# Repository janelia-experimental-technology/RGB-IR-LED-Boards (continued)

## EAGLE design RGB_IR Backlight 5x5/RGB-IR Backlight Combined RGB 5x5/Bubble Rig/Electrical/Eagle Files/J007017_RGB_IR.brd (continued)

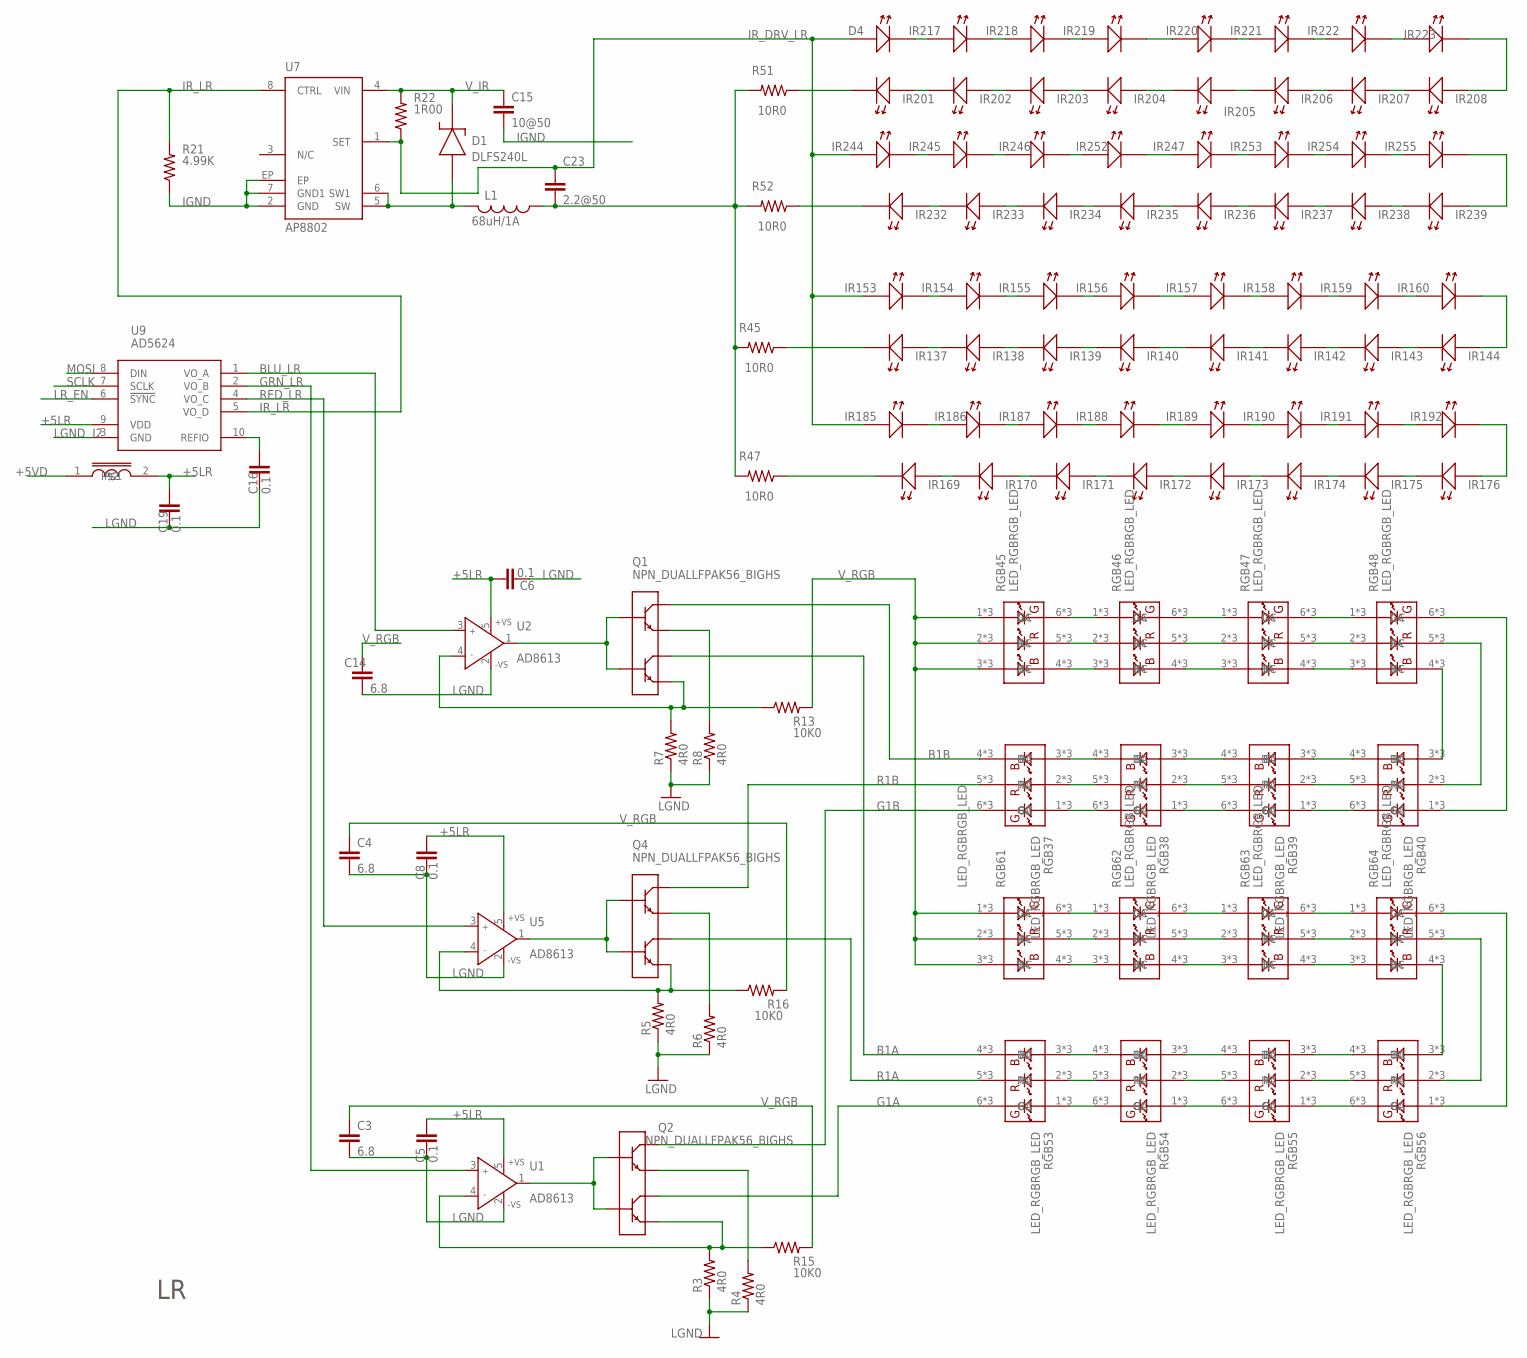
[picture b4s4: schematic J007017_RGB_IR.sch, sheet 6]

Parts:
C3, C4, C14: 6.8; 1210S
C5, C6, C8, C16, C19: 0.1; 0603S
C15: 10@50; 1210S
C23: 2.2@50; 1206S
D1: DLFS240L; PWRDI-123
D4: LEDLED_SFH4050_HEAT; LED_SFH4050_HEAT
I2: INDUCTOR0805S; 0805S
IR137, IR255: LEDLED_SFH4050; LED_SFH4050
IR138, IR139, IR140, IR141, IR142, IR143, IR144, IR153, IR155, IR156, IR157, IR158, IR159, IR160, IR169, IR170, IR171, IR172, IR173, IR174, IR175, IR176, IR185, IR186, IR187, IR188, IR189, IR190, IR191, IR192, IR201, IR202, IR203, IR204, IR205, IR206, IR207, IR208, IR217, IR218, IR219, IR220, IR221, IR222, IR223, IR232, IR233, IR234, IR235, IR236, IR237, IR238, IR239, IR244, IR245, IR246, IR247, IR252, IR253, IR254: LEDLED_SFH4050_HEAT; LED_SFH4050_HEAT
IR154: LEDLED_SFH4050_A; LED_SFH4045_HEAT_A
L1: 68uH/1A; SRU8043
Q1, Q2, Q4: NPN_DUALLFPAK56_BIGHS; LFPAK56_HS2
R3, R4, R5, R6, R7, R8: 4R0; 1812
R13, R15, R16: 10K0; 1206S
R21: 4.99K; 0805S
R22: 1R00; 1206S
R45, R47, R51, R52: 10R0; 1206S
RGB37, RGB38, RGB39, RGB40, RGB45, RGB46, RGB47, RGB48, RGB53, RGB54, RGB55, RGB56, RGB61, RGB62, RGB63, RGB64: LED_RGBRGB_LED; OVSPRGB_HS_FIXED
U1, U2, U5: AD8613; SOT23-5
U7: AP8802; SOIC8-EP
U9: AD5624; MSOP10

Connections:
+5LR: C5.1, C6.1, C8.1, C19.1, I2.2, U1.5 (+VS), U2.5 (+VS), U5.5 (+VS), U9.9 (VDD)
+5VD: I2.1; also elsewhere on the board
B1A: Q1.5 (C2), Q1.5A (C2), Q1.5A1 (C2), Q1.5B (C2), Q1.5C (C2), Q1.5C1 (C2), Q1.5C2 (C2), Q1.6 (C2), Q1.56 (C2), Q1.56A (C2), Q1.56B (C2), RGB53.4 (BC), RGB53.4A (BC), RGB53.4B (BC)
B1B: Q1.7 (C1), Q1.8 (C1), Q1.8A (C1), Q1.8B (C1), Q1.8C (C1), Q1.8C1 (C1), Q1.8C2 (C1), Q1.8C3 (C1), Q1.78 (C1), Q1.78A (C1), Q1.78B (C1), RGB37.4 (BC), RGB37.4A (BC), RGB37.4B (BC)
BLU_LR: U2.3 (IN+), U9.1 (VO_A)
G1A: Q2.5 (C2), Q2.5A (C2), Q2.5A1 (C2), Q2.5B (C2), Q2.5C (C2), Q2.5C1 (C2), Q2.5C2 (C2), Q2.6 (C2), Q2.56 (C2), Q2.56A (C2), Q2.56B (C2), RGB53.6 (GC), RGB53.6A (GC), RGB53.6B (GC)
G1B: Q2.7 (C1), Q2.8 (C1), Q2.8A (C1), Q2.8B (C1), Q2.8C (C1), Q2.8C1 (C1), Q2.8C2 (C1), Q2.8C3 (C1), Q2.78 (C1), Q2.78A (C1), Q2.78B (C1), RGB37.6 (GC), RGB37.6A (GC), RGB37.6B (GC)
GRN_LR: U1.3 (IN+), U9.2 (VO_B)
IGND: C15.2, R21.1, U7.2 (GND), U7.7 (GND1), U7.EP; also elsewhere on the board
IR_DRV_LR: C23.1, D4.A, D4.A1 (A), IR153.A, IR153.A1 (A), IR185.A, IR185.A1 (A), IR244.A, IR244.A1 (A), R22.1, U7.1 (SET)
IR_LR: R21.2, U7.8 (CTRL), U9.5 (VO_D)
IR_RET_UL3: C23.2, L1.1, R45.2, R47.2, R51.2, R52.2
LGND: C3.2, C4.2, C5.2, C6.2, C8.2, C14.2, C16.2, C19.2, R3.1, R4.1, R5.1, R6.1, R7.1, R8.1, U1.2 (-VS), U2.2 (-VS), U5.2 (-VS), U9.3 (GND); also elsewhere on the board
LR_EN: U9.6 (!SYNC); also elsewhere on the board
MOSI: U9.8 (DIN); also elsewhere on the board
unnamed: C16.1, U9.10 (REFIO)
unnamed: IR143.A, IR143.A1 (A), IR144.C (K), IR144.C1 (K)
unnamed: IR142.A, IR142.A1 (A), IR143.C (K), IR143.C1 (K)
unnamed: IR141.A, IR141.A1 (A), IR142.C (K), IR142.C1 (K)
unnamed: IR139.A, IR139.A1 (A), IR140.C (K), IR140.C1 (K)
unnamed: IR138.A, IR138.A1 (A), IR139.C (K), IR139.C1 (K)
unnamed: IR137.A, IR138.C (K), IR138.C1 (K)
unnamed: IR153.C (K), IR153.C1 (K), IR154.A, IR154.A1 (A)
unnamed: IR154.C (K), IR155.A, IR155.A1 (A)
unnamed: IR155.C (K), IR155.C1 (K), IR156.A, IR156.A1 (A)
unnamed: IR140.A, IR140.A1 (A), IR141.C (K), IR141.C1 (K)
unnamed: IR175.A, IR175.A1 (A), IR176.C (K), IR176.C1 (K)
unnamed: IR174.A, IR174.A1 (A), IR175.C (K), IR175.C1 (K)
unnamed: IR173.A, IR173.A1 (A), IR174.C (K), IR174.C1 (K)
unnamed: IR172.A, IR172.A1 (A), IR173.C (K), IR173.C1 (K)
unnamed: IR171.A, IR171.A1 (A), IR172.C (K), IR172.C1 (K)
unnamed: IR170.A, IR170.A1 (A), IR171.C (K), IR171.C1 (K)
unnamed: IR169.A, IR169.A1 (A), IR170.C (K), IR170.C1 (K)
unnamed: IR157.C (K), IR157.C1 (K), IR158.A, IR158.A1 (A)
unnamed: IR158.C (K), IR158.C1 (K), IR159.A, IR159.A1 (A)
unnamed: IR159.C (K), IR159.C1 (K), IR160.A, IR160.A1 (A)
unnamed: IR185.C (K), IR185.C1 (K), IR186.A, IR186.A1 (A)
unnamed: IR186.C (K), IR186.C1 (K), IR187.A, IR187.A1 (A)
unnamed: IR187.C (K), IR187.C1 (K), IR188.A, IR188.A1 (A)
unnamed: IR189.C (K), IR189.C1 (K), IR190.A, IR190.A1 (A)
unnamed: IR190.C (K), IR190.C1 (K), IR191.A, IR191.A1 (A)
unnamed: IR191.C (K), IR191.C1 (K), IR192.A, IR192.A1 (A)
unnamed: IR156.C (K), IR156.C1 (K), IR157.A, IR157.A1 (A)
unnamed: IR144.A, IR144.A1 (A), IR160.C (K), IR160.C1 (K)
unnamed: IR188.C (K), IR188.C1 (K), IR189.A, IR189.A1 (A)
unnamed: IR176.A, IR176.A1 (A), IR192.C (K), IR192.C1 (K)
unnamed: IR137.C (K), R45.1
unnamed: IR169.C (K), IR169.C1 (K), R47.1
unnamed: IR207.A, IR207.A1 (A), IR208.C (K), IR208.C1 (K)
unnamed: IR206.A, IR206.A1 (A), IR207.C (K), IR207.C1 (K)
unnamed: IR205.A, IR205.A1 (A), IR206.C (K), IR206.C1 (K)
unnamed: IR203.A, IR203.A1 (A), IR204.C (K), IR204.C1 (K)
unnamed: IR202.A, IR202.A1 (A), IR203.C (K), IR203.C1 (K)
unnamed: IR201.A, IR201.A1 (A), IR202.C (K), IR202.C1 (K)
unnamed: D4.C (K), D4.C1 (K), IR217.A, IR217.A1 (A)
unnamed: IR217.C (K), IR217.C1 (K), IR218.A, IR218.A1 (A)
unnamed: IR218.C (K), IR218.C1 (K), IR219.A, IR219.A1 (A)
unnamed: IR204.A, IR204.A1 (A), IR205.C (K), IR205.C1 (K)
unnamed: IR238.A, IR238.A1 (A), IR239.C (K), IR239.C1 (K)
unnamed: IR237.A, IR237.A1 (A), IR238.C (K), IR238.C1 (K)
unnamed: IR236.A, IR236.A1 (A), IR237.C (K), IR237.C1 (K)
unnamed: IR235.A, IR235.A1 (A), IR236.C (K), IR236.C1 (K)
unnamed: IR234.A, IR234.A1 (A), IR235.C (K), IR235.C1 (K)
unnamed: IR233.A, IR233.A1 (A), IR234.C (K), IR234.C1 (K)
unnamed: IR232.A, IR232.A1 (A), IR233.C (K), IR233.C1 (K)
unnamed: IR220.C (K), IR220.C1 (K), IR221.A, IR221.A1 (A)
unnamed: IR221.C (K), IR221.C1 (K), IR222.A, IR222.A1 (A)
unnamed: IR222.C (K), IR222.C1 (K), IR223.A, IR223.A1 (A)
unnamed: IR244.C (K), IR244.C1 (K), IR245.A, IR245.A1 (A)
unnamed: IR245.C (K), IR245.C1 (K), IR246.A, IR246.A1 (A)
unnamed: IR246.C (K), IR246.C1 (K), IR252.A, IR252.A1 (A)
unnamed: IR247.C (K), IR247.C1 (K), IR253.A, IR253.A1 (A)
unnamed: IR253.C (K), IR253.C1 (K), IR254.A, IR254.A1 (A)
unnamed: IR254.C (K), IR254.C1 (K), IR255.A
unnamed: IR219.C (K), IR219.C1 (K), IR220.A, IR220.A1 (A)
unnamed: IR208.A, IR208.A1 (A), IR223.C (K), IR223.C1 (K)
unnamed: IR247.A, IR247.A1 (A), IR252.C (K), IR252.C1 (K)
unnamed: IR239.A, IR239.A1 (A), IR255.C (K)
unnamed: IR201.C (K), IR201.C1 (K), R51.1
unnamed: IR232.C (K), IR232.C1 (K), R52.1
unnamed: Q1.3 (E2), R7.2, R13.1, U2.4 (IN-)
unnamed: D1.A, L1.2, U7.5 (SW), U7.6 (SW1)
unnamed: Q4.3 (E2), R5.2, R16.1, U5.4 (IN-)
unnamed: Q4.2 (B1), Q4.4 (B2), U5.1 (OUT)
unnamed: RGB45.6 (GC), RGB45.6A (GC), RGB45.6B (GC), RGB46.1 (GA), RGB46.1A (GA), RGB46.1B (GA)
unnamed: RGB45.5 (RC), RGB45.5A (RC), RGB45.5B (RC), RGB46.2 (RA), RGB46.2A (RA), RGB46.2B (RA)
unnamed: RGB45.4 (BC), RGB45.4A (BC), RGB45.4B (BC), RGB46.3 (BA), RGB46.3A (BA), RGB46.3B (BA)
unnamed: RGB46.6 (GC), RGB46.6A (GC), RGB46.6B (GC), RGB47.1 (GA), RGB47.1A (GA), RGB47.1B (GA)
unnamed: RGB46.5 (RC), RGB46.5A (RC), RGB46.5B (RC), RGB47.2 (RA), RGB47.2A (RA), RGB47.2B (RA)
unnamed: RGB46.4 (BC), RGB46.4A (BC), RGB46.4B (BC), RGB47.3 (BA), RGB47.3A (BA), RGB47.3B (BA)
unnamed: RGB47.6 (GC), RGB47.6A (GC), RGB47.6B (GC), RGB48.1 (GA), RGB48.1A (GA), RGB48.1B (GA)
unnamed: RGB47.5 (RC), RGB47.5A (RC), RGB47.5B (RC), RGB48.2 (RA), RGB48.2A (RA), RGB48.2B (RA)
unnamed: RGB47.4 (BC), RGB47.4A (BC), RGB47.4B (BC), RGB48.3 (BA), RGB48.3A (BA), RGB48.3B (BA)
unnamed: RGB40.1 (GA), RGB40.1A (GA), RGB40.1B (GA), RGB48.6 (GC), RGB48.6A (GC), RGB48.6B (GC)
unnamed: RGB40.2 (RA), RGB40.2A (RA), RGB40.2B (RA), RGB48.5 (RC), RGB48.5A (RC), RGB48.5B (RC)
unnamed: RGB40.3 (BA), RGB40.3A (BA), RGB40.3B (BA), RGB48.4 (BC), RGB48.4A (BC), RGB48.4B (BC)
unnamed: RGB39.1 (GA), RGB39.1A (GA), RGB39.1B (GA), RGB40.6 (GC), RGB40.6A (GC), RGB40.6B (GC)
unnamed: RGB39.2 (RA), RGB39.2A (RA), RGB39.2B (RA), RGB40.5 (RC), RGB40.5A (RC), RGB40.5B (RC)
unnamed: RGB39.3 (BA), RGB39.3A (BA), RGB39.3B (BA), RGB40.4 (BC), RGB40.4A (BC), RGB40.4B (BC)
unnamed: RGB38.1 (GA), RGB38.1A (GA), RGB38.1B (GA), RGB39.6 (GC), RGB39.6A (GC), RGB39.6B (GC)
unnamed: RGB38.2 (RA), RGB38.2A (RA), RGB38.2B (RA), RGB39.5 (RC), RGB39.5A (RC), RGB39.5B (RC)
unnamed: RGB38.3 (BA), RGB38.3A (BA), RGB38.3B (BA), RGB39.4 (BC), RGB39.4A (BC), RGB39.4B (BC)
unnamed: RGB37.1 (GA), RGB37.1A (GA), RGB37.1B (GA), RGB38.6 (GC), RGB38.6A (GC), RGB38.6B (GC)
unnamed: RGB37.2 (RA), RGB37.2A (RA), RGB37.2B (RA), RGB38.5 (RC), RGB38.5A (RC), RGB38.5B (RC)
unnamed: RGB37.3 (BA), RGB37.3A (BA), RGB37.3B (BA), RGB38.4 (BC), RGB38.4A (BC), RGB38.4B (BC)
unnamed: Q2.3 (E2), R3.2, R15.1, U1.4 (IN-)
unnamed: Q2.2 (B1), Q2.4 (B2), U1.1 (OUT)
unnamed: RGB61.6 (GC), RGB61.6A (GC), RGB61.6B (GC), RGB62.1 (GA), RGB62.1A (GA), RGB62.1B (GA)
unnamed: RGB61.5 (RC), RGB61.5A (RC), RGB61.5B (RC), RGB62.2 (RA), RGB62.2A (RA), RGB62.2B (RA)
unnamed: RGB61.4 (BC), RGB61.4A (BC), RGB61.4B (BC), RGB62.3 (BA), RGB62.3A (BA), RGB62.3B (BA)
unnamed: RGB62.6 (GC), RGB62.6A (GC), RGB62.6B (GC), RGB63.1 (GA), RGB63.1A (GA), RGB63.1B (GA)
unnamed: RGB62.5 (RC), RGB62.5A (RC), RGB62.5B (RC), RGB63.2 (RA), RGB63.2A (RA), RGB63.2B (RA)
unnamed: RGB62.4 (BC), RGB62.4A (BC), RGB62.4B (BC), RGB63.3 (BA), RGB63.3A (BA), RGB63.3B (BA)
unnamed: RGB63.6 (GC), RGB63.6A (GC), RGB63.6B (GC), RGB64.1 (GA), RGB64.1A (GA), RGB64.1B (GA)
unnamed: RGB63.5 (RC), RGB63.5A (RC), RGB63.5B (RC), RGB64.2 (RA), RGB64.2A (RA), RGB64.2B (RA)
unnamed: RGB63.4 (BC), RGB63.4A (BC), RGB63.4B (BC), RGB64.3 (BA), RGB64.3A (BA), RGB64.3B (BA)
unnamed: RGB56.1 (GA), RGB56.1A (GA), RGB56.1B (GA), RGB64.6 (GC), RGB64.6A (GC), RGB64.6B (GC)
unnamed: RGB56.2 (RA), RGB56.2A (RA), RGB56.2B (RA), RGB64.5 (RC), RGB64.5A (RC), RGB64.5B (RC)
unnamed: RGB56.3 (BA), RGB56.3A (BA), RGB56.3B (BA), RGB64.4 (BC), RGB64.4A (BC), RGB64.4B (BC)
unnamed: RGB55.1 (GA), RGB55.1A (GA), RGB55.1B (GA), RGB56.6 (GC), RGB56.6A (GC), RGB56.6B (GC)
unnamed: RGB55.2 (RA), RGB55.2A (RA), RGB55.2B (RA), RGB56.5 (RC), RGB56.5A (RC), RGB56.5B (RC)
unnamed: RGB55.3 (BA), RGB55.3A (BA), RGB55.3B (BA), RGB56.4 (BC), RGB56.4A (BC), RGB56.4B (BC)
unnamed: RGB54.1 (GA), RGB54.1A (GA), RGB54.1B (GA), RGB55.6 (GC), RGB55.6A (GC), RGB55.6B (GC)
unnamed: RGB54.2 (RA), RGB54.2A (RA), RGB54.2B (RA), RGB55.5 (RC), RGB55.5A (RC), RGB55.5B (RC)
unnamed: RGB54.3 (BA), RGB54.3A (BA), RGB54.3B (BA), RGB55.4 (BC), RGB55.4A (BC), RGB55.4B (BC)
unnamed: RGB53.1 (GA), RGB53.1A (GA), RGB53.1B (GA), RGB54.6 (GC), RGB54.6A (GC), RGB54.6B (GC)
unnamed: RGB53.2 (RA), RGB53.2A (RA), RGB53.2B (RA), RGB54.5 (RC), RGB54.5A (RC), RGB54.5B (RC)
unnamed: RGB53.3 (BA), RGB53.3A (BA), RGB53.3B (BA), RGB54.4 (BC), RGB54.4A (BC), RGB54.4B (BC)
unnamed: Q1.2 (B1), Q1.4 (B2), U2.1 (OUT)
unnamed: Q1.1 (E1), R8.2
unnamed: Q4.1 (E1), R6.2
unnamed: Q2.1 (E1), R4.2
R1A: Q4.5 (C2), Q4.5A (C2), Q4.5A1 (C2), Q4.5B (C2), Q4.5C (C2), Q4.5C1 (C2), Q4.5C2 (C2), Q4.6 (C2), Q4.56 (C2), Q4.56A (C2), Q4.56B (C2), RGB53.5 (RC), RGB53.5A (RC), RGB53.5B (RC)
R1B: Q4.7 (C1), Q4.8 (C1), Q4.8A (C1), Q4.8B (C1), Q4.8C (C1), Q4.8C1 (C1), Q4.8C2 (C1), Q4.8C3 (C1), Q4.78 (C1), Q4.78A (C1), Q4.78B (C1), RGB37.5 (RC), RGB37.5A (RC), RGB37.5B (RC)
RED_LR: U5.3 (IN+), U9.4 (VO_C)
SCLK: U9.7 (SCLK); also elsewhere on the board
V_IR: C15.1, D1.K, R22.2, U7.4 (VIN); also elsewhere on the board
V_RGB: C3.1, C4.1, C14.1, R13.2, R15.2, R16.2, RGB45.1 (GA), RGB45.1A (GA), RGB45.1B (GA), RGB45.2 (RA), RGB45.2A (RA), RGB45.2B (RA), RGB45.3 (BA), RGB45.3A (BA), RGB45.3B (BA), RGB61.1 (GA), RGB61.1A (GA), RGB61.1B (GA), RGB61.2 (RA), RGB61.2A (RA), RGB61.2B (RA), RGB61.3 (BA), RGB61.3A (BA), RGB61.3B (BA); also elsewhere on the board

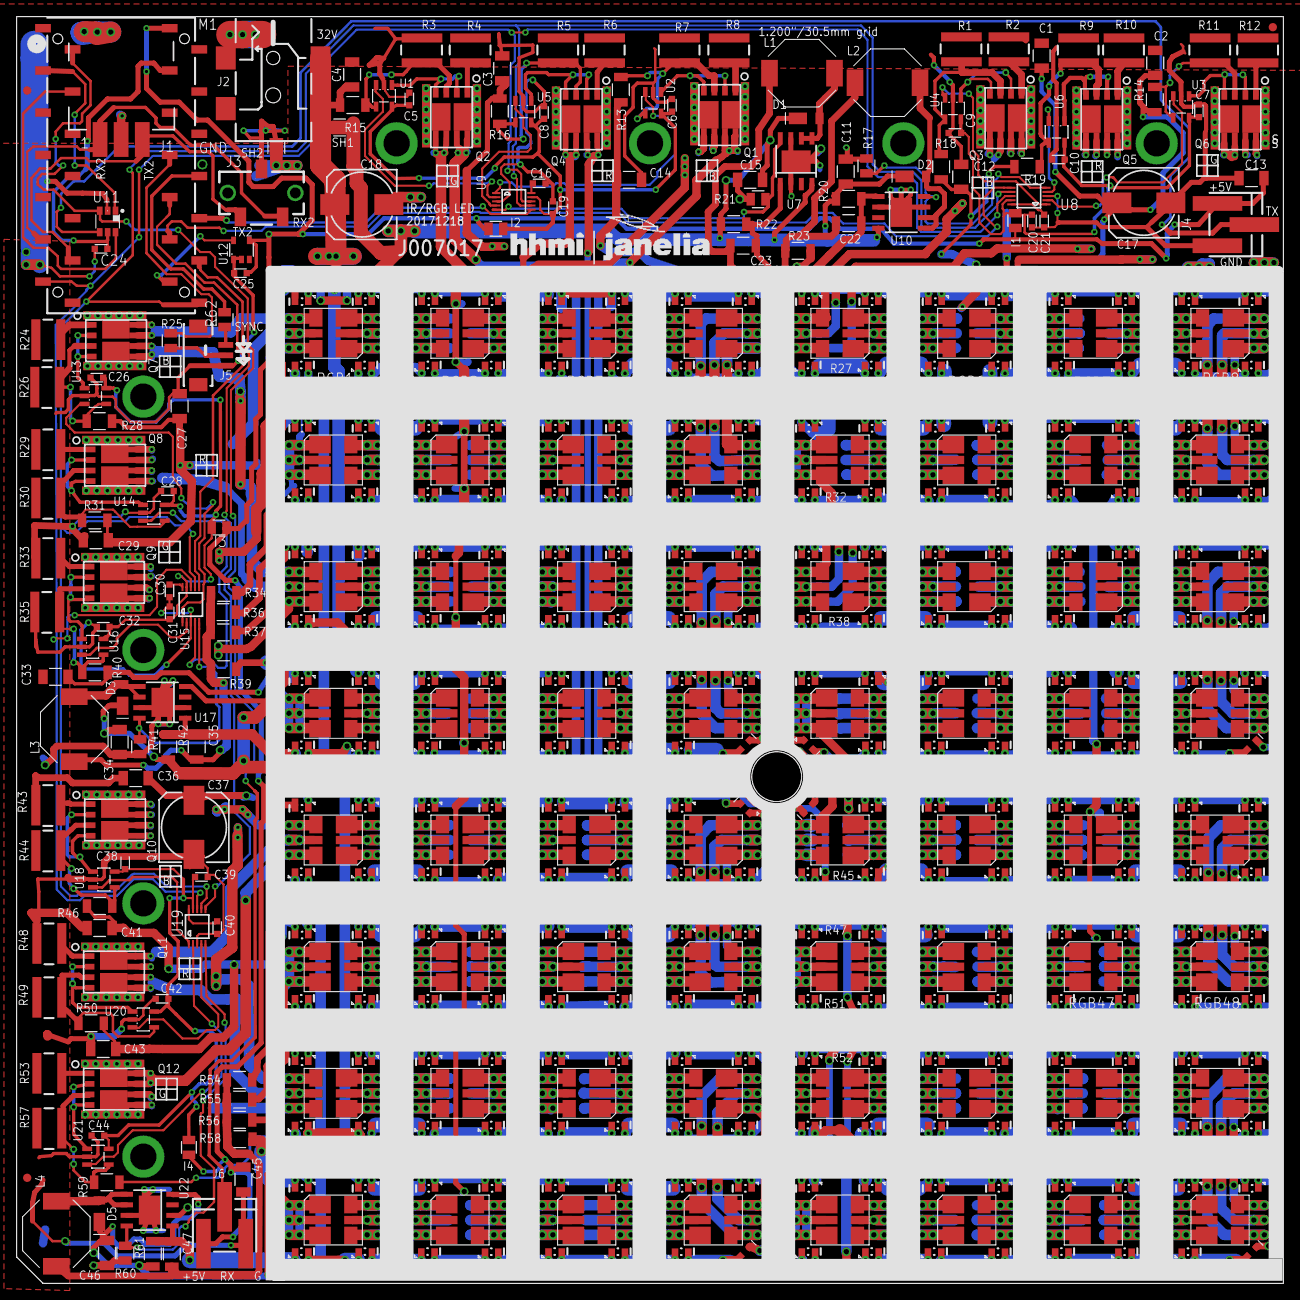
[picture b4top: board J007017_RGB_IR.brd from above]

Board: 2 copper layers, 152.4 x 152.4 mm, 488 parts (0 on the bottom side), 543 nets.

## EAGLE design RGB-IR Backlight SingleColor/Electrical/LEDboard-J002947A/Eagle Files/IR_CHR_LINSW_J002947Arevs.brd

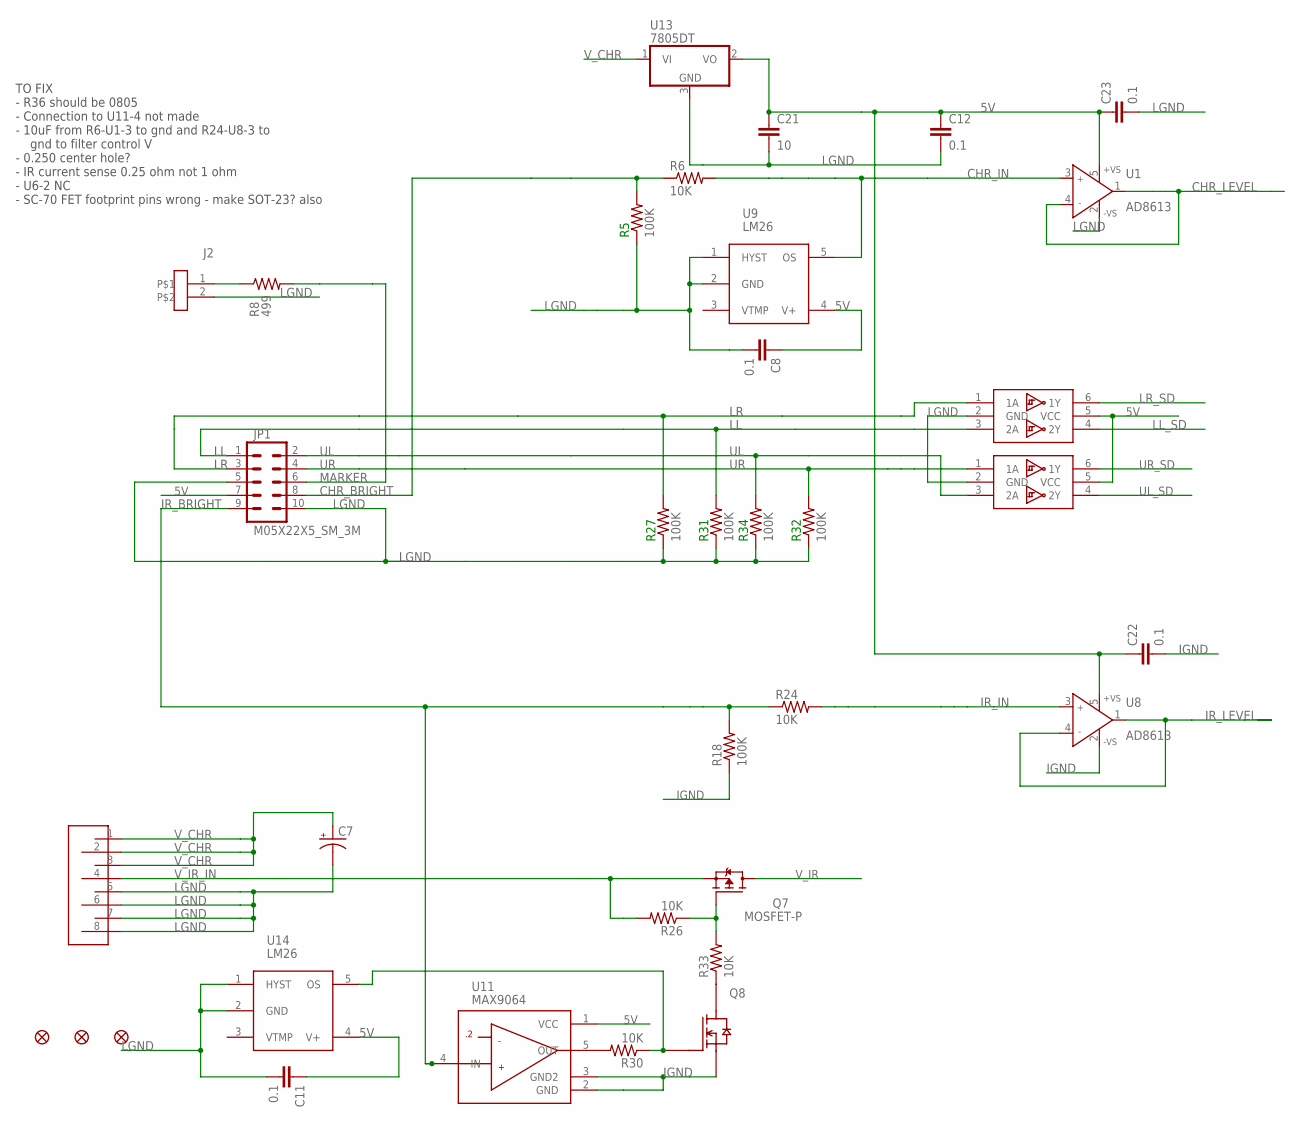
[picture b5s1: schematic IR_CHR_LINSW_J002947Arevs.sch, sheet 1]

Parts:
C7: CAP_POLG; PANASONIC_G
C8, C11, C12, C22, C23: 0.1; 0603S
C21: 10; 0805S
FID1, FID2, FID3: FIDUCIAL1.5X3; FIDUCIAL-1.5X3
J1: CON8PHOENIX1778829; PHOENIX1778829
J2: CON2DF3-2\; DF3-2_RA
JP1: M05X22X5_SM_3M; 2X5-SHROUDED_SMD_3M
Q7: MOSFET-P; SO-8POWERPAK
Q8: MOSFET-N; SC-70
R5, R18, R27, R31, R32, R34: 100K; 0603S
R6, R24, R26, R30, R33: 10K; 0603S
R8: 499; 0603S
U1, U8: AD8613; SOT23-5
U9, U14: LM26; SOT23-5
U10, U12: 74DUAL14; SOT23-6
U11: MAX9064; SOT23-5L
U13: 7805DT; TO252

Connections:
5V: C8.1, C11.1, C12.1, C21.1, C22.1, C23.1, JP1.7, U1.5 (+VS), U8.5 (+VS), U9.4 (V+), U10.5 (VCC), U11.1 (VCC), U12.5 (VCC), U13.2 (VO), U14.4 (V+)
CHR_BRIGHT: JP1.8, R5.2, R6.1
CHR_IN: R6.2, U1.3 (IN+), U9.5 (OS)
CHR_LEVEL: U1.1 (OUT), U1.4 (IN-); also elsewhere on the board
IGND: C22.2, Q8.2 (S), R18.1, U8.2 (-VS), U11.2 (GND), U11.3 (GND2); also elsewhere on the board
IR_BRIGHT: JP1.9, R18.2, R24.1, U11.4 (IN)
IR_IN: R24.2, U8.3 (IN+)
IR_LEVEL: U8.1 (OUT), U8.4 (IN-); also elsewhere on the board
LGND: C7.-, C8.2, C11.2, C12.2, C21.2, C23.2, J1.5, J1.6, J1.7, J1.8, J2.2, JP1.5, JP1.10, R5.1, R27.1, R31.1, R32.1, R34.1, U1.2 (-VS), U9.1 (HYST), U9.2 (GND), U10.2 (GND), U12.2 (GND), U13.3 (GND), U14.1 (HYST), U14.2 (GND); also elsewhere on the board
LL: JP1.1, R31.2, U10.3 (2A)
LL_SD: U10.4 (2Y); also elsewhere on the board
LR: JP1.3, R27.2, U10.1 (1A)
LR_SD: U10.6 (1Y); also elsewhere on the board
MARKER: JP1.6, R8.2
unnamed: J2.1, R8.1
unnamed: Q7.4 (G), R26.1, R33.2
unnamed: Q8.1 (G), R30.1, U14.5 (OS)
unnamed: Q8.3 (D), R33.1
unnamed: R30.2, U11.5 (OUT)
UL: JP1.2, R34.2, U12.3 (2A)
UL_SD: U12.4 (2Y); also elsewhere on the board
UR: JP1.4, R32.2, U12.1 (1A)
UR_SD: U12.6 (1Y); also elsewhere on the board
V_CHR: C7.+, J1.1, J1.2, J1.3, U13.1 (VI); also elsewhere on the board
V_IR: Q7.5 (D), Q7.6 (D), Q7.7 (D), Q7.8 (D), Q7.9 (D); also elsewhere on the board
V_IR_IN: J1.4, Q7.1 (S), Q7.2 (S), Q7.3 (S), R26.2

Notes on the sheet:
TO FIX - R36 should be 0805 - Connection to U11-4 not made - 10uF from R6-U1-3 to gnd and R24-U8-3 to gnd to filter control V - 0.250 center hole? - IR current sense 0.25 ohm not 1 ohm - U6-2 NC - SC-70 FET footprint pins wrong - make SOT-23? also

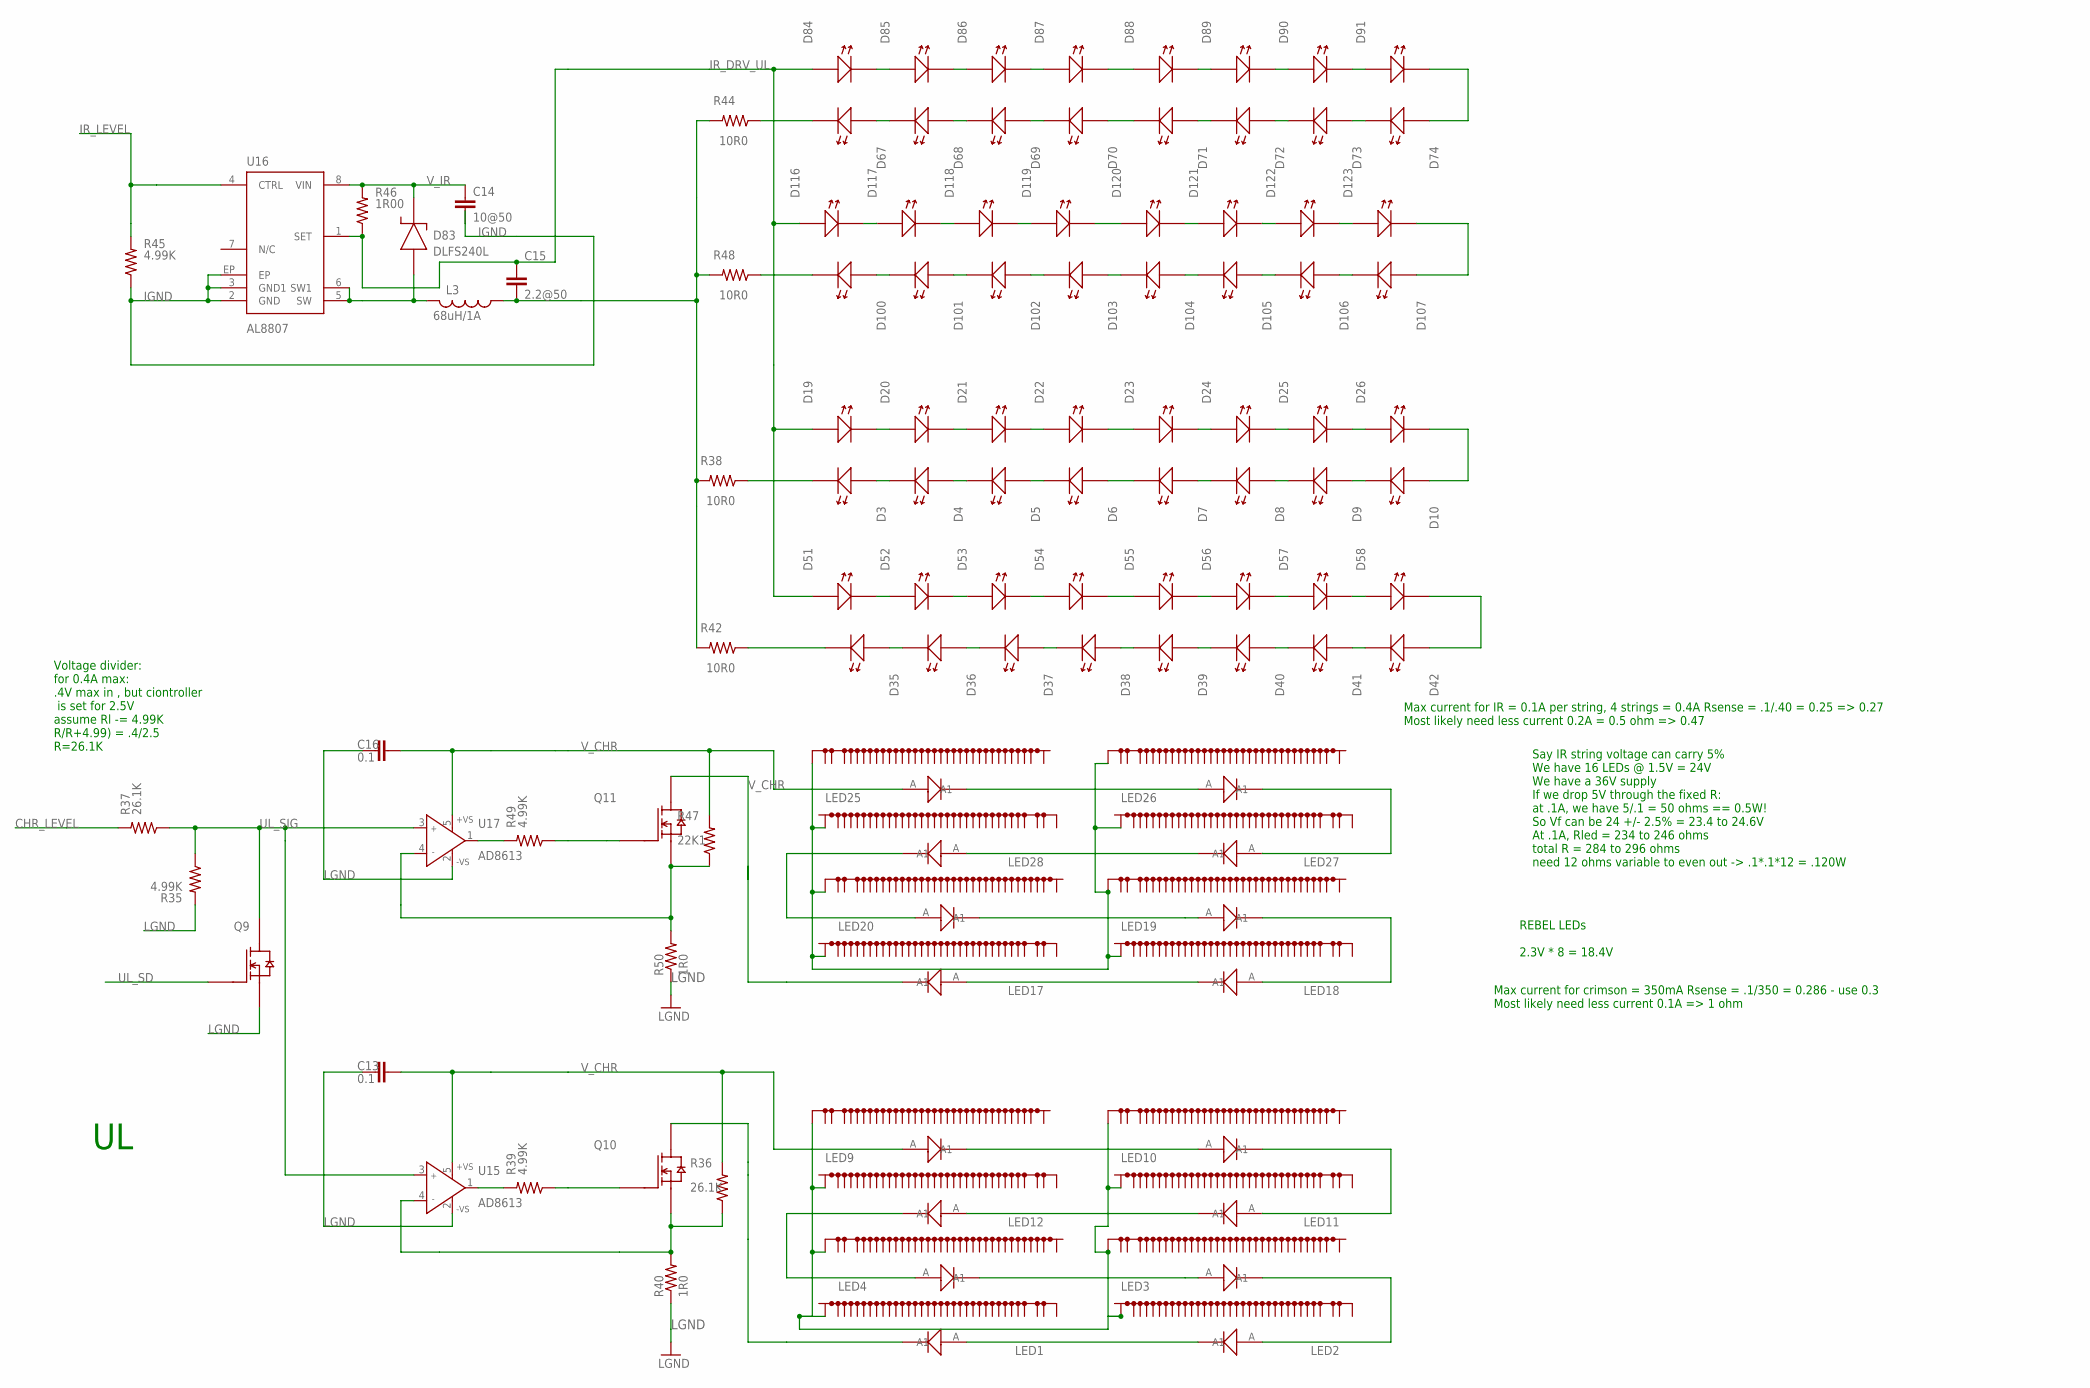
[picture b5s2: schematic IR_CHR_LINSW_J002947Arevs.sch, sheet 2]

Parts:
C13, C16: 0.1; 0603S
C14: 10@50; 1206S
C15: 2.2@50; 1206S
D3, D4, D5, D6, D7, D8, D9, D10, D19, D20, D21, D22, D23, D24, D25, D26, D35, D36, D37, D38, D39, D40, D41, D42, D51, D52, D53, D54, D55, D56, D57, D58, D67, D68, D69, D70, D71, D72, D73, D74, D84, D85, D86, D87, D88, D89, D90, D91, D100, D101, D102, D103, D104, D105, D106, D107, D116, D117, D118, D119, D120, D121, D122: LEDLED_SFH4050_HEAT; LED_SFH4050_HEAT
D83: DLFS240L; PWRDI-123
D123: LEDLED_SFH4050_A; LED_SFH4045_HEAT_A
L3: 68uH/1A; SRU8043
LED1, LED2, LED3, LED4, LED9, LED10, LED11, LED12, LED17, LED18, LED19, LED20, LED25, LED26, LED27, LED28: REBEL_0603OG_LED_W0603_EVEN_12; OG_LED_W0603_EVEN_12
Q9: MOSFET-N; SC-70
Q10, Q11: MOSFET-NTI252_HS; TO252_HS
R35, R39, R49: 4.99K; 0603S
R36, R37: 26.1K; 0603S
R38, R42, R44, R48: 10R0; 1206S
R40, R50: 1R0; 2512WIDE_HS1
R45: 4.99K; 0805S
R46: 1R00; 1206S
R47: 22K1; 0805S
U15, U17: AD8613; SOT23-5
U16: AL8807; MSOP8-EP

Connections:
CHR_LEVEL: R37.2; also elsewhere on the board
IGND: C14.2, R45.1, U16.2 (GND), U16.3 (GND1), U16.EP; also elsewhere on the board
IR_DRV_UL: C15.1, D19.A, D19.A1 (A), D51.A, D51.A1 (A), D84.A, D84.A1 (A), D116.A, D116.A1 (A), R46.1, U16.1 (SET)
IR_LEVEL: R45.2, U16.4 (CTRL); also elsewhere on the board
IR_RET_UL: C15.2, L3.1, R38.2, R42.2, R44.2, R48.2
LGND: C13.2, C16.2, Q9.2 (S), R35.2, R40.1, R40.1A (1), R40.1A1 (1), R40.1B (1), R40.1B1 (1), R40.1C (1), R50.1, R50.1A (1), R50.1A1 (1), R50.1B (1), R50.1B1 (1), R50.1C (1), U15.2 (-VS), U17.2 (-VS); also elsewhere on the board
unnamed: D9.A, D9.A1 (A), D10.C (K), D10.C1 (K)
unnamed: D8.A, D8.A1 (A), D9.C (K), D9.C1 (K)
unnamed: D73.A, D73.A1 (A), D74.C (K), D74.C1 (K)
unnamed: D72.A, D72.A1 (A), D73.C (K), D73.C1 (K)
unnamed: D71.A, D71.A1 (A), D72.C (K), D72.C1 (K)
unnamed: D69.A, D69.A1 (A), D70.C (K), D70.C1 (K)
unnamed: D68.A, D68.A1 (A), D69.C (K), D69.C1 (K)
unnamed: D67.A, D67.A1 (A), D68.C (K), D68.C1 (K)
unnamed: D7.A, D7.A1 (A), D8.C (K), D8.C1 (K)
unnamed: D5.A, D5.A1 (A), D6.C (K), D6.C1 (K)
unnamed: D4.A, D4.A1 (A), D5.C (K), D5.C1 (K)
unnamed: D3.A, D3.A1 (A), D4.C (K), D4.C1 (K)
unnamed: D19.C (K), D19.C1 (K), D20.A, D20.A1 (A)
unnamed: D84.C (K), D84.C1 (K), D85.A, D85.A1 (A)
unnamed: D20.C (K), D20.C1 (K), D21.A, D21.A1 (A)
unnamed: D85.C (K), D85.C1 (K), D86.A, D86.A1 (A)
unnamed: D86.C (K), D86.C1 (K), D87.A, D87.A1 (A)
unnamed: D70.A, D70.A1 (A), D71.C (K), D71.C1 (K)
unnamed: D106.A, D106.A1 (A), D107.C (K), D107.C1 (K)
unnamed: D105.A, D105.A1 (A), D106.C (K), D106.C1 (K)
unnamed: D104.A, D104.A1 (A), D105.C (K), D105.C1 (K)
unnamed: D103.A, D103.A1 (A), D104.C (K), D104.C1 (K)
unnamed: D102.A, D102.A1 (A), D103.C (K), D103.C1 (K)
unnamed: D21.C (K), D21.C1 (K), D22.A, D22.A1 (A)
unnamed: D6.A, D6.A1 (A), D7.C (K), D7.C1 (K)
unnamed: D41.A, D41.A1 (A), D42.C (K), D42.C1 (K)
unnamed: D40.A, D40.A1 (A), D41.C (K), D41.C1 (K)
unnamed: D39.A, D39.A1 (A), D40.C (K), D40.C1 (K)
unnamed: D101.A, D101.A1 (A), D102.C (K), D102.C1 (K)
unnamed: D38.A, D38.A1 (A), D39.C (K), D39.C1 (K)
unnamed: D37.A, D37.A1 (A), D38.C (K), D38.C1 (K)
unnamed: D100.A, D100.A1 (A), D101.C (K), D101.C1 (K)
unnamed: D88.C (K), D88.C1 (K), D89.A, D89.A1 (A)
unnamed: D89.C (K), D89.C1 (K), D90.A, D90.A1 (A)
unnamed: D36.A, D36.A1 (A), D37.C (K), D37.C1 (K)
unnamed: D90.C (K), D90.C1 (K), D91.A, D91.A1 (A)
unnamed: D35.A, D35.A1 (A), D36.C (K), D36.C1 (K)
unnamed: D23.C (K), D23.C1 (K), D24.A, D24.A1 (A)
unnamed: D24.C (K), D24.C1 (K), D25.A, D25.A1 (A)
unnamed: D25.C (K), D25.C1 (K), D26.A, D26.A1 (A)
unnamed: D51.C (K), D51.C1 (K), D52.A, D52.A1 (A)
unnamed: D52.C (K), D52.C1 (K), D53.A, D53.A1 (A)
unnamed: D53.C (K), D53.C1 (K), D54.A, D54.A1 (A)
unnamed: D55.C (K), D55.C1 (K), D56.A, D56.A1 (A)
unnamed: D56.C (K), D56.C1 (K), D57.A, D57.A1 (A)
unnamed: D57.C (K), D57.C1 (K), D58.A, D58.A1 (A)
unnamed: D116.C (K), D116.C1 (K), D117.A, D117.A1 (A)
unnamed: D22.C (K), D22.C1 (K), D23.A, D23.A1 (A)
unnamed: D117.C (K), D117.C1 (K), D118.A, D118.A1 (A)
unnamed: D10.A, D10.A1 (A), D26.C (K), D26.C1 (K)
unnamed: D54.C (K), D54.C1 (K), D55.A, D55.A1 (A)
unnamed: D118.C (K), D118.C1 (K), D119.A, D119.A1 (A)
unnamed: D3.C (K), D3.C1 (K), R38.1
unnamed: D42.A, D42.A1 (A), D58.C (K), D58.C1 (K)
unnamed: D35.C (K), D35.C1 (K), R42.1
unnamed: D67.C (K), D67.C1 (K), R44.1
unnamed: D120.C (K), D120.C1 (K), D121.A, D121.A1 (A)
unnamed: R49.2, U17.1 (OUT)
unnamed: D121.C (K), D121.C1 (K), D122.A, D122.A1 (A)
unnamed: D122.C (K), D122.C1 (K), D123.A, D123.A1 (A)
unnamed: Q10.2 (S), R36.1, R40.2, U15.4 (IN-)
unnamed: D83.A, L3.2, U16.5 (SW), U16.6 (SW1)
unnamed: D87.C (K), D87.C1 (K), D88.A, D88.A1 (A)
unnamed: D74.A, D74.A1 (A), D91.C (K), D91.C1 (K)
unnamed: LED9.C (K1), LED10.A (A1)
unnamed: D119.C (K), D119.C1 (K), D120.A, D120.A1 (A)
unnamed: LED10.C (K1), LED11.A (A1)
unnamed: D107.A, D107.A1 (A), D123.C (K)
unnamed: LED11.C (K1), LED12.A (A1)
unnamed: D100.C (K), D100.C1 (K), R48.1
unnamed: LED4.A (A1), LED12.C (K1)
unnamed: LED3.A (A1), LED4.C (K1)
unnamed: LED2.A (A1), LED3.C (K1)
unnamed: Q10.1 (G), R39.1
unnamed: LED1.A (A1), LED2.C (K1)
unnamed: R39.2, U15.1 (OUT)
unnamed: LED25.C (K1), LED26.A (A1)
unnamed: LED26.C (K1), LED27.A (A1)
unnamed: LED27.C (K1), LED28.A (A1)
unnamed: LED20.A (A1), LED28.C (K1)
unnamed: LED19.A (A1), LED20.C (K1)
unnamed: LED18.A (A1), LED19.C (K1)
unnamed: LED17.A (A1), LED18.C (K1)
unnamed: Q11.2 (S), R47.1, R50.2, U17.4 (IN-)
unnamed: Q11.1 (G), R49.1
Q11: LED1.C (K1), Q10.3 (D), Q10.3S (D), Q10.P$1 (D), Q10.P$2 (D), Q10.P$3 (D), Q10.P$4 (D), Q10.P$5 (D), Q10.P$6 (D), Q10.P$7 (D), Q10.P$8 (D), Q10.P$9 (D), Q10.P$10 (D), Q10.P$11 (D), Q10.P$12 (D)
Q12: LED17.C (K1), Q11.3 (D), Q11.3S (D), Q11.P$1 (D), Q11.P$2 (D), Q11.P$3 (D), Q11.P$4 (D), Q11.P$5 (D), Q11.P$6 (D), Q11.P$7 (D), Q11.P$8 (D), Q11.P$9 (D), Q11.P$10 (D), Q11.P$11 (D), Q11.P$12 (D)
TH: LED1.TH1 (TH), LED1.TH@38 (TH), LED1.TH@39 (TH), LED1.TH@40 (TH), LED1.TH@41 (TH), LED1.TH@42 (TH), LED1.TH@43 (TH), LED1.TH@44 (TH), LED1.TH@45 (TH), LED1.TH@46 (TH), LED1.TH@47 (TH), LED1.TH@48 (TH), LED1.TH@49 (TH), LED1.TH@50 (TH), LED1.TH@51 (TH), LED1.TH@52 (TH), LED1.TH@53 (TH), LED1.TH@54 (TH), LED1.TH@55 (TH), LED1.TH@56 (TH), LED1.TH@57 (TH), LED1.TH@58 (TH), LED1.TH@59 (TH), LED1.TH@60 (TH), LED1.TH@61 (TH), LED1.TH@62 (TH), LED1.TH@63 (TH), LED1.TH@64 (TH), LED1.TH@65 (TH), LED1.TH@66 (TH), LED1.TH@67 (TH), LED1.TH@68 (TH), LED1.TH@69 (TH), LED1.TH@70 (TH), LED2.TH1 (TH), LED2.TH@38 (TH), LED2.TH@39 (TH), LED2.TH@40 (TH), LED2.TH@41 (TH), LED2.TH@42 (TH), LED2.TH@43 (TH), LED2.TH@44 (TH), LED2.TH@45 (TH), LED2.TH@46 (TH), LED2.TH@47 (TH), LED2.TH@48 (TH), LED2.TH@49 (TH), LED2.TH@50 (TH), LED2.TH@51 (TH), LED2.TH@52 (TH), LED2.TH@53 (TH), LED2.TH@54 (TH), LED2.TH@55 (TH), LED2.TH@56 (TH), LED2.TH@57 (TH), LED2.TH@58 (TH), LED2.TH@59 (TH), LED2.TH@60 (TH), LED2.TH@61 (TH), LED2.TH@62 (TH), LED2.TH@63 (TH), LED2.TH@64 (TH), LED2.TH@65 (TH), LED2.TH@66 (TH), LED2.TH@67 (TH), LED2.TH@68 (TH), LED2.TH@69 (TH), LED2.TH@70 (TH), LED3.TH1 (TH), LED3.TH@38 (TH), LED3.TH@39 (TH), LED3.TH@40 (TH), LED3.TH@41 (TH), LED3.TH@42 (TH), LED3.TH@43 (TH), LED3.TH@44 (TH), LED3.TH@45 (TH), LED3.TH@46 (TH), LED3.TH@47 (TH), LED3.TH@48 (TH), LED3.TH@49 (TH), LED3.TH@50 (TH), LED3.TH@51 (TH), LED3.TH@52 (TH), LED3.TH@53 (TH), LED3.TH@54 (TH), LED3.TH@55 (TH), LED3.TH@56 (TH), LED3.TH@57 (TH), LED3.TH@58 (TH), LED3.TH@59 (TH), LED3.TH@60 (TH), LED3.TH@61 (TH), LED3.TH@62 (TH), LED3.TH@63 (TH), LED3.TH@64 (TH), LED3.TH@65 (TH), LED3.TH@66 (TH), LED3.TH@67 (TH), LED3.TH@68 (TH), LED3.TH@69 (TH), LED3.TH@70 (TH), LED4.TH1 (TH), LED4.TH@38 (TH), LED4.TH@39 (TH), LED4.TH@40 (TH), LED4.TH@41 (TH), LED4.TH@42 (TH), LED4.TH@43 (TH), LED4.TH@44 (TH), LED4.TH@45 (TH), LED4.TH@46 (TH), LED4.TH@47 (TH), LED4.TH@48 (TH), LED4.TH@49 (TH), LED4.TH@50 (TH), LED4.TH@51 (TH), LED4.TH@52 (TH), LED4.TH@53 (TH), LED4.TH@54 (TH), LED4.TH@55 (TH), LED4.TH@56 (TH), LED4.TH@57 (TH), LED4.TH@58 (TH), LED4.TH@59 (TH), LED4.TH@60 (TH), LED4.TH@61 (TH), LED4.TH@62 (TH), LED4.TH@63 (TH), LED4.TH@64 (TH), LED4.TH@65 (TH), LED4.TH@66 (TH), LED4.TH@67 (TH), LED4.TH@68 (TH), LED4.TH@69 (TH), LED4.TH@70 (TH), LED9.TH1 (TH), LED9.TH@38 (TH), LED9.TH@39 (TH), LED9.TH@40 (TH), LED9.TH@41 (TH), LED9.TH@42 (TH), LED9.TH@43 (TH), LED9.TH@44 (TH), LED9.TH@45 (TH), LED9.TH@46 (TH), LED9.TH@47 (TH), LED9.TH@48 (TH), LED9.TH@49 (TH), LED9.TH@50 (TH), LED9.TH@51 (TH), LED9.TH@52 (TH), LED9.TH@53 (TH), LED9.TH@54 (TH), LED9.TH@55 (TH), LED9.TH@56 (TH), LED9.TH@57 (TH), LED9.TH@58 (TH), LED9.TH@59 (TH), LED9.TH@60 (TH), LED9.TH@61 (TH), LED9.TH@62 (TH), LED9.TH@63 (TH), LED9.TH@64 (TH), LED9.TH@65 (TH), LED9.TH@66 (TH), LED9.TH@67 (TH), LED9.TH@68 (TH), LED9.TH@69 (TH), LED9.TH@70 (TH), LED10.TH1 (TH), LED10.TH@38 (TH), LED10.TH@39 (TH), LED10.TH@40 (TH), LED10.TH@41 (TH), LED10.TH@42 (TH), LED10.TH@43 (TH), LED10.TH@44 (TH), LED10.TH@45 (TH), LED10.TH@46 (TH), LED10.TH@47 (TH), LED10.TH@48 (TH), LED10.TH@49 (TH), LED10.TH@50 (TH), LED10.TH@51 (TH), LED10.TH@52 (TH), LED10.TH@53 (TH), LED10.TH@54 (TH), LED10.TH@55 (TH), LED10.TH@56 (TH), LED10.TH@57 (TH), LED10.TH@58 (TH), LED10.TH@59 (TH), LED10.TH@60 (TH), LED10.TH@61 (TH), LED10.TH@62 (TH), LED10.TH@63 (TH), LED10.TH@64 (TH), LED10.TH@65 (TH), LED10.TH@66 (TH), LED10.TH@67 (TH), LED10.TH@68 (TH), LED10.TH@69 (TH), LED10.TH@70 (TH), LED11.TH1 (TH), LED11.TH@38 (TH), LED11.TH@39 (TH), LED11.TH@40 (TH), LED11.TH@41 (TH), LED11.TH@42 (TH), LED11.TH@43 (TH), LED11.TH@44 (TH), LED11.TH@45 (TH), LED11.TH@46 (TH), LED11.TH@47 (TH), LED11.TH@48 (TH), LED11.TH@49 (TH), LED11.TH@50 (TH), LED11.TH@51 (TH), LED11.TH@52 (TH), LED11.TH@53 (TH), LED11.TH@54 (TH), LED11.TH@55 (TH), LED11.TH@56 (TH), LED11.TH@57 (TH), LED11.TH@58 (TH), LED11.TH@59 (TH), LED11.TH@60 (TH), LED11.TH@61 (TH), LED11.TH@62 (TH), LED11.TH@63 (TH), LED11.TH@64 (TH), LED11.TH@65 (TH), LED11.TH@66 (TH), LED11.TH@67 (TH), LED11.TH@68 (TH), LED11.TH@69 (TH), LED11.TH@70 (TH), LED12.TH1 (TH), LED12.TH@38 (TH), LED12.TH@39 (TH), LED12.TH@40 (TH), LED12.TH@41 (TH), LED12.TH@42 (TH), LED12.TH@43 (TH), LED12.TH@44 (TH), LED12.TH@45 (TH), LED12.TH@46 (TH), LED12.TH@47 (TH), LED12.TH@48 (TH), LED12.TH@49 (TH), LED12.TH@50 (TH), LED12.TH@51 (TH), LED12.TH@52 (TH), LED12.TH@53 (TH), LED12.TH@54 (TH), LED12.TH@55 (TH), LED12.TH@56 (TH), LED12.TH@57 (TH), LED12.TH@58 (TH), LED12.TH@59 (TH), LED12.TH@60 (TH), LED12.TH@61 (TH), LED12.TH@62 (TH), LED12.TH@63 (TH), LED12.TH@64 (TH), LED12.TH@65 (TH), LED12.TH@66 (TH), LED12.TH@67 (TH), LED12.TH@68 (TH), LED12.TH@69 (TH), LED12.TH@70 (TH), LED17.TH1 (TH), LED17.TH@38 (TH), LED17.TH@39 (TH), LED17.TH@40 (TH), LED17.TH@41 (TH), LED17.TH@42 (TH), LED17.TH@43 (TH), LED17.TH@44 (TH), LED17.TH@45 (TH), LED17.TH@46 (TH), LED17.TH@47 (TH), LED17.TH@48 (TH), LED17.TH@49 (TH), LED17.TH@50 (TH), LED17.TH@51 (TH), LED17.TH@52 (TH), LED17.TH@53 (TH), LED17.TH@54 (TH), LED17.TH@55 (TH), LED17.TH@56 (TH), LED17.TH@57 (TH), LED17.TH@58 (TH), LED17.TH@59 (TH), LED17.TH@60 (TH), LED17.TH@61 (TH), LED17.TH@62 (TH), LED17.TH@63 (TH), LED17.TH@64 (TH), LED17.TH@65 (TH), LED17.TH@66 (TH), LED17.TH@67 (TH), LED17.TH@68 (TH), LED17.TH@69 (TH), LED17.TH@70 (TH), LED18.TH1 (TH), LED18.TH@38 (TH), LED18.TH@39 (TH), LED18.TH@40 (TH), LED18.TH@41 (TH), LED18.TH@42 (TH), LED18.TH@43 (TH), LED18.TH@44 (TH), LED18.TH@45 (TH), LED18.TH@46 (TH), LED18.TH@47 (TH), LED18.TH@48 (TH), LED18.TH@49 (TH), LED18.TH@50 (TH), LED18.TH@51 (TH), LED18.TH@52 (TH), LED18.TH@53 (TH), LED18.TH@54 (TH), LED18.TH@55 (TH), LED18.TH@56 (TH), LED18.TH@57 (TH), LED18.TH@58 (TH), LED18.TH@59 (TH), LED18.TH@60 (TH), LED18.TH@61 (TH), LED18.TH@62 (TH), LED18.TH@63 (TH), LED18.TH@64 (TH), LED18.TH@65 (TH), LED18.TH@66 (TH), LED18.TH@67 (TH), LED18.TH@68 (TH), LED18.TH@69 (TH), LED18.TH@70 (TH), LED19.TH1 (TH), LED19.TH@38 (TH), LED19.TH@39 (TH), LED19.TH@40 (TH), LED19.TH@41 (TH), LED19.TH@42 (TH), LED19.TH@43 (TH), LED19.TH@44 (TH), LED19.TH@45 (TH), LED19.TH@46 (TH), LED19.TH@47 (TH), LED19.TH@48 (TH), LED19.TH@49 (TH), LED19.TH@50 (TH), LED19.TH@51 (TH), LED19.TH@52 (TH), LED19.TH@53 (TH), LED19.TH@54 (TH), LED19.TH@55 (TH), LED19.TH@56 (TH), LED19.TH@57 (TH), LED19.TH@58 (TH), LED19.TH@59 (TH), LED19.TH@60 (TH), LED19.TH@61 (TH), LED19.TH@62 (TH), LED19.TH@63 (TH), LED19.TH@64 (TH), LED19.TH@65 (TH), LED19.TH@66 (TH), LED19.TH@67 (TH), LED19.TH@68 (TH), LED19.TH@69 (TH), LED19.TH@70 (TH), LED20.TH1 (TH), LED20.TH@38 (TH), LED20.TH@39 (TH), LED20.TH@40 (TH), LED20.TH@41 (TH), LED20.TH@42 (TH), LED20.TH@43 (TH), LED20.TH@44 (TH), LED20.TH@45 (TH), LED20.TH@46 (TH), LED20.TH@47 (TH), LED20.TH@48 (TH), LED20.TH@49 (TH), LED20.TH@50 (TH), LED20.TH@51 (TH), LED20.TH@52 (TH), LED20.TH@53 (TH), LED20.TH@54 (TH), LED20.TH@55 (TH)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; also elsewhere on the board
UL_SD: Q9.1 (G); also elsewhere on the board
UL_SIG: Q9.3 (D), R35.1, R37.1, U15.3 (IN+), U17.3 (IN+)
V_CHR: C13.1, C16.1, LED9.A (A1), LED25.A (A1), R36.2, R47.2, U15.5 (+VS), U17.5 (+VS); also elsewhere on the board
V_IR: C14.1, D83.K, R46.2, U16.8 (VIN); also elsewhere on the board

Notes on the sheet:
Say IR string voltage can carry 5% We have 16 LEDs @ 1.5V = 24V We have a 36V supply If we drop 5V through the fixed R: at .1A, we have 5/.1 = 50 ohms == 0.5W! So Vf can be 24 +/- 2.5% = 23.4 to 24.6V At .1A, Rled = 234 to 246 ohms total R = 284 to 296 ohms need 12 ohms variable to even out -> .1*.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
REBEL LEDs 2.3V * 8 = 18.4V
Max current for crimson = 350mA Rsense = .1/350 = 0.286 - use 0.3 Most likely need less current 0.1A => 1 ohm
Max current for IR = 0.1A per string, 4 strings = 0.4A Rsense = .1/.40 = 0.25 => 0.27 Most likely need less current 0.2A = 0.5 ohm => 0.47
Voltage divider: for 0.4A max: .4V max in , but ciontroller is set for 2.5V assume Rl -= 4.99K R/R+4.99) = .4/2.5 R=26.1K
